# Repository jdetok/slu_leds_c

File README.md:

# SLU Fleur de Lis Lights Display
designed by Justin DeKock - Fall 2025
#
`
# [SEE USER GUIDE/INSTRUCTIONS HERE](USERGUIDE.md)
- ## [Demo Video](https://youtu.be/l19p7q0IOvI)
# [SEE BILL OF MATERIALS (ELECTRONICS PARTS) HERE](BOM.md)

## Firmware
- the device's [firmware](firmware/) is written in C++ 
- built and uploaded to Arduino with [PlatformIO](https://platformio.org/) [VSCode extension](https://platformio.org/install/ide?install=vscode)

## Printed Circuit Board (PCB)
- the [electrical schematic and the PCB](pcb/) were designed in [KiCad](https://www.kicad.org/)

## repo organization
- ### pcb/ 
    - contains KiCAD project with shematic/PCB files 
- ### firmware/
    - contains C++ firmware that gets uploaded to the arduino
    - project

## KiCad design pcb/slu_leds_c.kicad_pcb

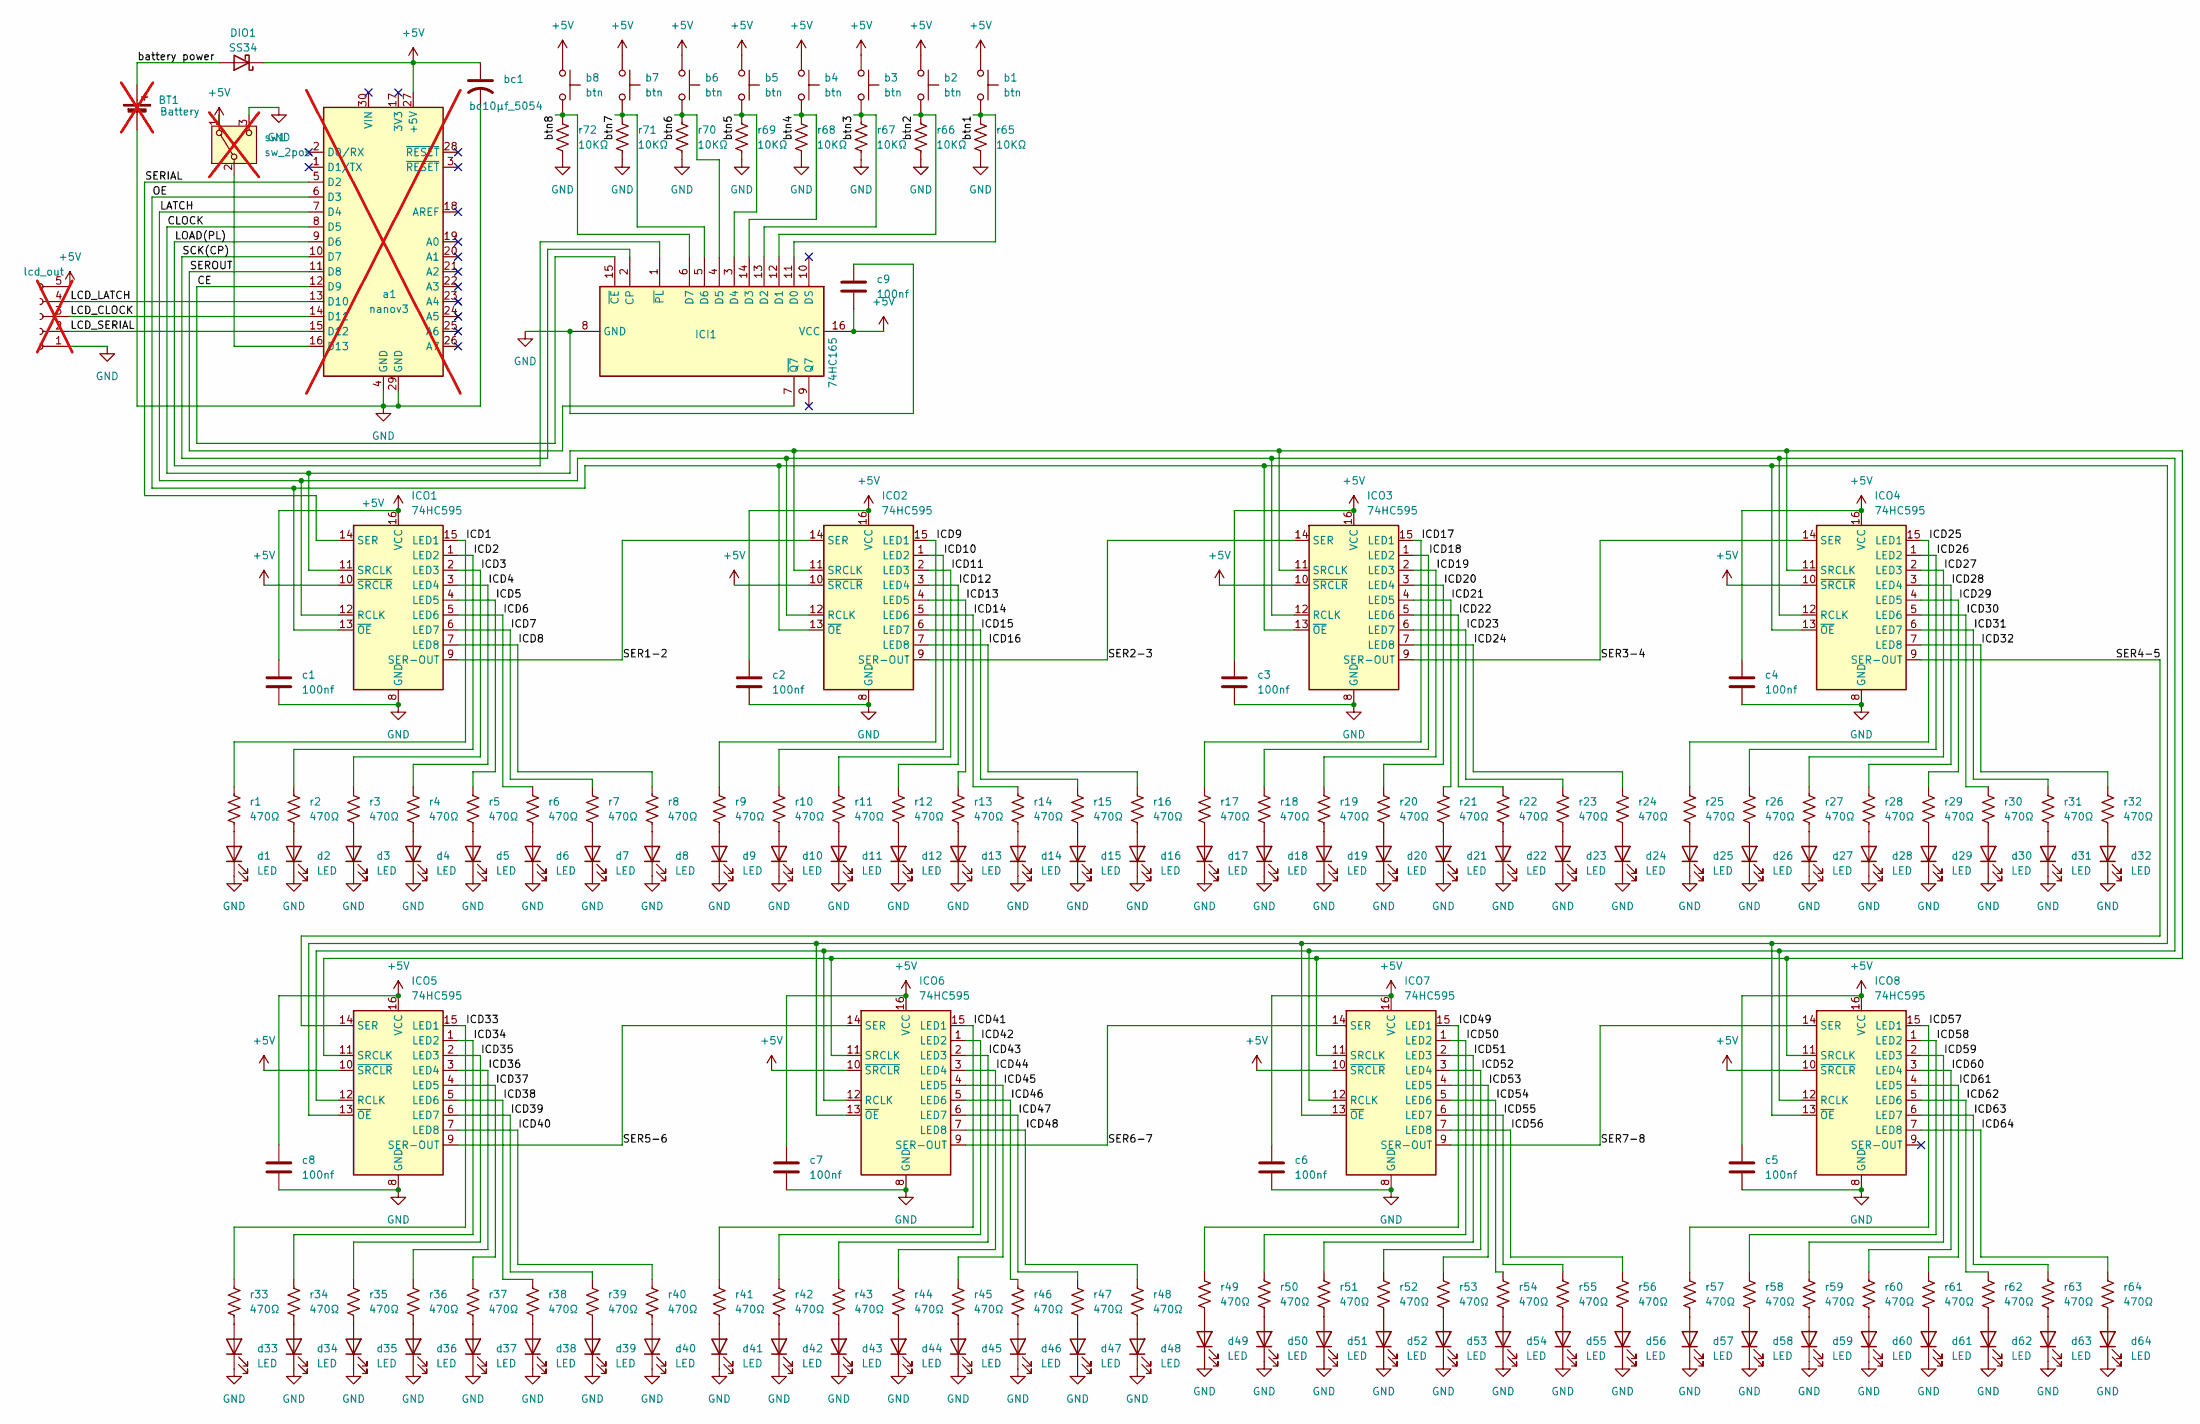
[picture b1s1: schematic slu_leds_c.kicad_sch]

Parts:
BT1: Battery; btry_18650_foirot; not fitted
DIO1: SS34; D_SMA; LCSC Part # C8678
ICI1: 74HC165; sop16_hc165; LCSC Part # C61060
ICO1, ICO2, ICO3, ICO4, ICO5, ICO6, ICO7, ICO8: 74HC595; sop16_hc595; LCSC Part # C79097
J1: lcd_out; 5pin_2.54; not fitted
a1: nanov3; not fitted
b1, b2, b3, b4, b5, b6, b7, b8: btn; btn_4x3; LCSC Part # C720477
bc1: bc10µf_5054; CP_Elec_4x5.4; LCSC Part # C3343
c1, c2, c3, c4, c5, c6, c7, c8, c9: 100nf; cap1206; LCSC Part # C24497
d1, d2, d3, d4, d5, d6, d7, d8, d9, d10, d11, d12, d13, d14, d15, d16, d17, d18, d19, d20, d21, d22, d23, d24, d25, d26, d27, d28, d29, d30, d31, d32, d33, d34, d35, d36, d37, d38, d39, d40, d41, d42, d43, d44, d45, d46, d47, d48, d49, d50, d51, d52, d53, d54, d55, d56, d57, d58, d59, d60, d61, d62, d63, d64: LED; blue_led_3528; LCSC Part # C50327302
r1, r2, r3, r4, r5, r6, r7, r8, r9, r10, r11, r12, r13, r14, r15, r16, r17, r18, r19, r20, r21, r22, r23, r24, r25, r26, r27, r28, r29, r30, r31, r32, r33, r34, r35, r36, r37, r38, r39, r40, r41, r42, r43, r44, r45, r46, r47, r48, r49, r50, r51, r52, r53, r54, r55, r56, r57, r58, r59, r60, r61, r62, r63, r64: 470Ω; r_470Ω_1206; LCSC Part # C4502
r65, r66, r67, r68, r69, r70, r71, r72: 10KΩ; r_10KΩ_1206; LCSC Part # C17902
sw1: sw_2pos; sw_2pos_spdt; not fitted

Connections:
+5V: DIO1.1 (K), ICI1.16 (VCC), ICO1.10 (~SRCLR), ICO1.16 (VCC), ICO2.10 (~SRCLR), ICO2.16 (VCC), ICO3.10 (~SRCLR), ICO3.16 (VCC), ICO4.10 (~SRCLR), ICO4.16 (VCC), ICO5.10 (~SRCLR), ICO5.16 (VCC), ICO6.10 (~SRCLR), ICO6.16 (VCC), ICO7.10 (~SRCLR), ICO7.16 (VCC), ICO8.10 (~SRCLR), ICO8.16 (VCC), J1.5, a1.27 (+5V), b1.1, b2.1, b3.1, b4.1, b5.1, b6.1, b7.1, b8.1, bc1.1, c1.1, c2.1, c3.1, c4.1, c5.1, c6.1, c7.1, c8.1, c9.2, sw1.1 (A); also elsewhere on the board
/CE: ICI1.15 (~CE), a1.12 (D9)
/CLOCK: ICO1.11 (SRCLK), ICO2.11 (SRCLK), ICO3.11 (SRCLK), ICO4.11 (SRCLK), ICO5.11 (SRCLK), ICO6.11 (SRCLK), ICO7.11 (SRCLK), ICO8.11 (SRCLK), a1.8 (D5)
/ICD1: ICO1.15 (LED1), r1.2
/ICD2: ICO1.1 (LED2), r2.2
/ICD3: ICO1.2 (LED3), r3.2
/ICD4: ICO1.3 (LED4), r4.2
/ICD5: ICO1.4 (LED5), r5.2
/ICD6: ICO1.5 (LED6), r6.2
/ICD7: ICO1.6 (LED7), r7.2
/ICD8: ICO1.7 (LED8), r8.2
/ICD9: ICO2.15 (LED1), r9.2
/ICD10: ICO2.1 (LED2), r10.2
/ICD11: ICO2.2 (LED3), r11.2
/ICD12: ICO2.3 (LED4), r12.2
/ICD13: ICO2.4 (LED5), r13.2
/ICD14: ICO2.5 (LED6), r14.2
/ICD15: ICO2.6 (LED7), r15.2
/ICD16: ICO2.7 (LED8), r16.2
/ICD17: ICO3.15 (LED1), r17.2
/ICD18: ICO3.1 (LED2), r18.2
/ICD19: ICO3.2 (LED3), r19.2
/ICD20: ICO3.3 (LED4), r20.2
/ICD21: ICO3.4 (LED5), r21.2
/ICD22: ICO3.5 (LED6), r22.2
/ICD23: ICO3.6 (LED7), r23.2
/ICD24: ICO3.7 (LED8), r24.2
/ICD25: ICO4.15 (LED1), r25.2
/ICD26: ICO4.1 (LED2), r26.2
/ICD27: ICO4.2 (LED3), r27.2
/ICD28: ICO4.3 (LED4), r28.2
/ICD29: ICO4.4 (LED5), r29.2
/ICD30: ICO4.5 (LED6), r30.2
/ICD31: ICO4.6 (LED7), r31.2
/ICD32: ICO4.7 (LED8), r32.2
/ICD33: ICO5.15 (LED1), r33.2
/ICD34: ICO5.1 (LED2), r34.2
/ICD35: ICO5.2 (LED3), r35.2
/ICD36: ICO5.3 (LED4), r36.2
/ICD37: ICO5.4 (LED5), r37.2
/ICD38: ICO5.5 (LED6), r38.2
/ICD39: ICO5.6 (LED7), r39.2
/ICD40: ICO5.7 (LED8), r40.2
/ICD41: ICO6.15 (LED1), r41.2
/ICD42: ICO6.1 (LED2), r42.2
/ICD43: ICO6.2 (LED3), r43.2
/ICD44: ICO6.3 (LED4), r44.2
/ICD45: ICO6.4 (LED5), r45.2
/ICD46: ICO6.5 (LED6), r46.2
/ICD47: ICO6.6 (LED7), r47.2
/ICD48: ICO6.7 (LED8), r48.2
/ICD49: ICO7.15 (LED1), r49.2
/ICD50: ICO7.1 (LED2), r50.2
/ICD51: ICO7.2 (LED3), r51.2
/ICD52: ICO7.3 (LED4), r52.2
/ICD53: ICO7.4 (LED5), r53.2
/ICD54: ICO7.5 (LED6), r54.2
/ICD55: ICO7.6 (LED7), r55.2
/ICD56: ICO7.7 (LED8), r56.2
/ICD57: ICO8.15 (LED1), r57.2
/ICD58: ICO8.1 (LED2), r58.2
/ICD59: ICO8.2 (LED3), r59.2
/ICD60: ICO8.3 (LED4), r60.2
/ICD61: ICO8.4 (LED5), r61.2
/ICD62: ICO8.5 (LED6), r62.2
/ICD63: ICO8.6 (LED7), r63.2
/ICD64: ICO8.7 (LED8), r64.2
/LATCH: ICO1.12 (RCLK), ICO2.12 (RCLK), ICO3.12 (RCLK), ICO4.12 (RCLK), ICO5.12 (RCLK), ICO6.12 (RCLK), ICO7.12 (RCLK), ICO8.12 (RCLK), a1.7 (D4)
/LCD_CLOCK: J1.3, a1.14 (D11)
/LCD_LATCH: J1.4, a1.13 (D10)
/LCD_SERIAL: J1.2, a1.15 (D12)
/LOAD(PL): ICI1.1 (~PL), a1.9 (D6)
/OE: ICO1.13 (~OE), ICO2.13 (~OE), ICO3.13 (~OE), ICO4.13 (~OE), ICO5.13 (~OE), ICO6.13 (~OE), ICO7.13 (~OE), ICO8.13 (~OE), a1.6 (D3)
/SCK(CP): ICI1.2 (CP), a1.10 (D7)
/SER1-2: ICO1.9 (SER-OUT), ICO2.14 (SER)
/SER2-3: ICO2.9 (SER-OUT), ICO3.14 (SER)
/SER3-4: ICO3.9 (SER-OUT), ICO4.14 (SER)
/SER4-5: ICO4.9 (SER-OUT), ICO5.14 (SER)
/SER5-6: ICO5.9 (SER-OUT), ICO6.14 (SER)
/SER6-7: ICO6.9 (SER-OUT), ICO7.14 (SER)
/SER7-8: ICO7.9 (SER-OUT), ICO8.14 (SER)
/SERIAL: ICO1.14 (SER), a1.5 (D2)
/SEROUT: ICI1.7 (~Q7), a1.11 (D8)
/btn1: ICI1.11 (D0), b1.2, r65.1
/btn2: ICI1.12 (D1), b2.2, r66.1
/btn3: ICI1.13 (D2), b3.2, r67.1
/btn4: ICI1.14 (D3), b4.2, r68.1
/btn5: ICI1.3 (D4), b5.2, r69.1
/btn6: ICI1.4 (D5), b6.2, r70.1
/btn7: ICI1.5 (D6), b7.2, r71.1
/btn8: ICI1.6 (D7), b8.2, r72.1
GND: BT1.2 (-), ICI1.8 (GND), ICO1.8 (GND), ICO2.8 (GND), ICO3.8 (GND), ICO4.8 (GND), ICO5.8 (GND), ICO6.8 (GND), ICO7.8 (GND), ICO8.8 (GND), J1.1, a1.4 (GND), a1.29 (GND), bc1.2, c1.2, c2.2, c3.2, c4.2, c5.2, c6.2, c7.2, c8.2, c9.1, d1.1 (K), d2.1 (K), d3.1 (K), d4.1 (K), d5.1 (K), d6.1 (K), d7.1 (K), d8.1 (K), d9.1 (K), d10.1 (K), d11.1 (K), d12.1 (K), d13.1 (K), d14.1 (K), d15.1 (K), d16.1 (K), d17.1 (K), d18.1 (K), d19.1 (K), d20.1 (K), d21.1 (K), d22.1 (K), d23.1 (K), d24.1 (K), d25.1 (K), d26.1 (K), d27.1 (K), d28.1 (K), d29.1 (K), d30.1 (K), d31.1 (K), d32.1 (K), d33.1 (K), d34.1 (K), d35.1 (K), d36.1 (K), d37.1 (K), d38.1 (K), d39.1 (K), d40.1 (K), d41.1 (K), d42.1 (K), d43.1 (K), d44.1 (K), d45.1 (K), d46.1 (K), d47.1 (K), d48.1 (K), d49.1 (K), d50.1 (K), d51.1 (K), d52.1 (K), d53.1 (K), d54.1 (K), d55.1 (K), d56.1 (K), d57.1 (K), d58.1 (K), d59.1 (K), d60.1 (K), d61.1 (K), d62.1 (K), d63.1 (K), d64.1 (K), r65.2, r66.2, r67.2, r68.2, r69.2, r70.2, r71.2, r72.2, sw1.3 (C); also elsewhere on the board
unnamed: BT1.1 (+), DIO1.2 (A)
unnamed: a1.16 (D13), sw1.2 (B)
unnamed: d1.2 (A), r1.1
unnamed: d2.2 (A), r2.1
unnamed: d3.2 (A), r3.1
unnamed: d4.2 (A), r4.1
unnamed: d5.2 (A), r5.1
unnamed: d6.2 (A), r6.1
unnamed: d7.2 (A), r7.1
unnamed: d8.2 (A), r8.1
unnamed: d9.2 (A), r9.1
unnamed: d10.2 (A), r10.1
unnamed: d11.2 (A), r11.1
unnamed: d12.2 (A), r12.1
unnamed: d13.2 (A), r13.1
unnamed: d14.2 (A), r14.1
unnamed: d15.2 (A), r15.1
unnamed: d16.2 (A), r16.1
unnamed: d17.2 (A), r17.1
unnamed: d18.2 (A), r18.1
unnamed: d19.2 (A), r19.1
unnamed: d20.2 (A), r20.1
unnamed: d21.2 (A), r21.1
unnamed: d22.2 (A), r22.1
unnamed: d23.2 (A), r23.1
unnamed: d24.2 (A), r24.1
unnamed: d25.2 (A), r25.1
unnamed: d26.2 (A), r26.1
unnamed: d27.2 (A), r27.1
unnamed: d28.2 (A), r28.1
unnamed: d29.2 (A), r29.1
unnamed: d30.2 (A), r30.1
unnamed: d31.2 (A), r31.1
unnamed: d32.2 (A), r32.1
unnamed: d33.2 (A), r33.1
unnamed: d34.2 (A), r34.1
unnamed: d35.2 (A), r35.1
unnamed: d36.2 (A), r36.1
unnamed: d37.2 (A), r37.1
unnamed: d38.2 (A), r38.1
unnamed: d39.2 (A), r39.1
unnamed: d40.2 (A), r40.1
unnamed: d41.2 (A), r41.1
unnamed: d42.2 (A), r42.1
unnamed: d43.2 (A), r43.1
unnamed: d44.2 (A), r44.1
unnamed: d45.2 (A), r45.1
unnamed: d46.2 (A), r46.1
unnamed: d47.2 (A), r47.1
unnamed: d48.2 (A), r48.1
unnamed: d49.2 (A), r49.1
unnamed: d50.2 (A), r50.1
unnamed: d51.2 (A), r51.1
unnamed: d52.2 (A), r52.1
unnamed: d53.2 (A), r53.1
unnamed: d54.2 (A), r54.1
unnamed: d55.2 (A), r55.1
unnamed: d56.2 (A), r56.1
unnamed: d57.2 (A), r57.1
unnamed: d58.2 (A), r58.1
unnamed: d59.2 (A), r59.1
unnamed: d60.2 (A), r60.1
unnamed: d61.2 (A), r61.1
unnamed: d62.2 (A), r62.1
unnamed: d63.2 (A), r63.1
unnamed: d64.2 (A), r64.1

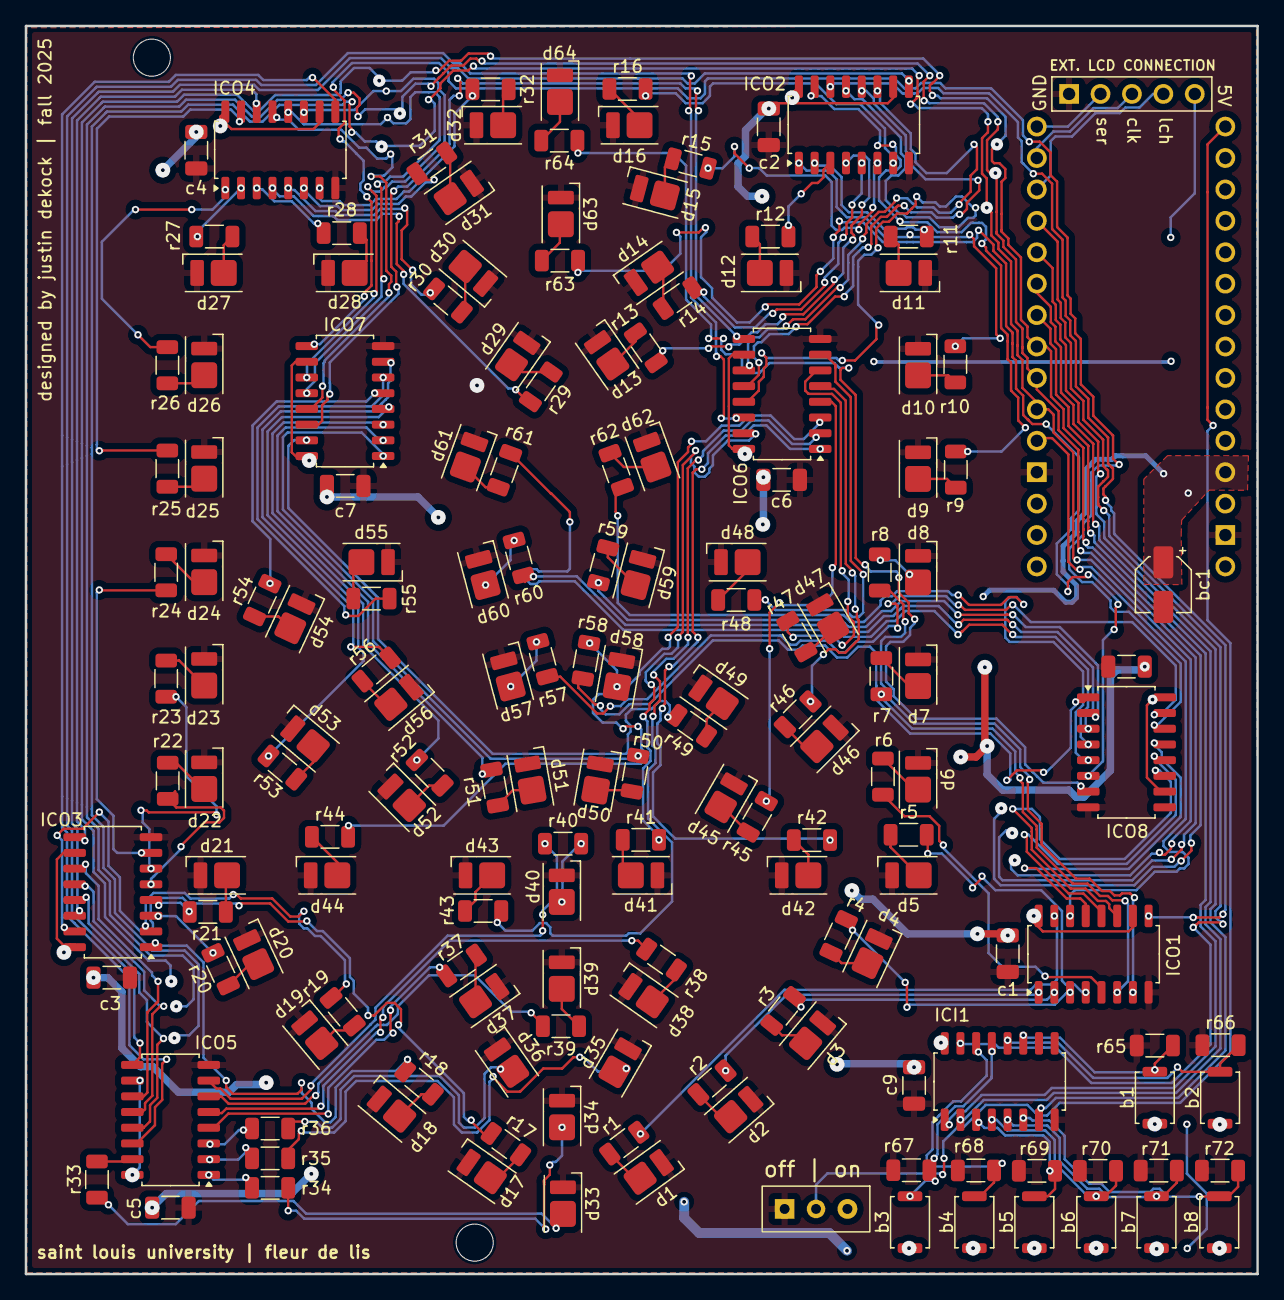
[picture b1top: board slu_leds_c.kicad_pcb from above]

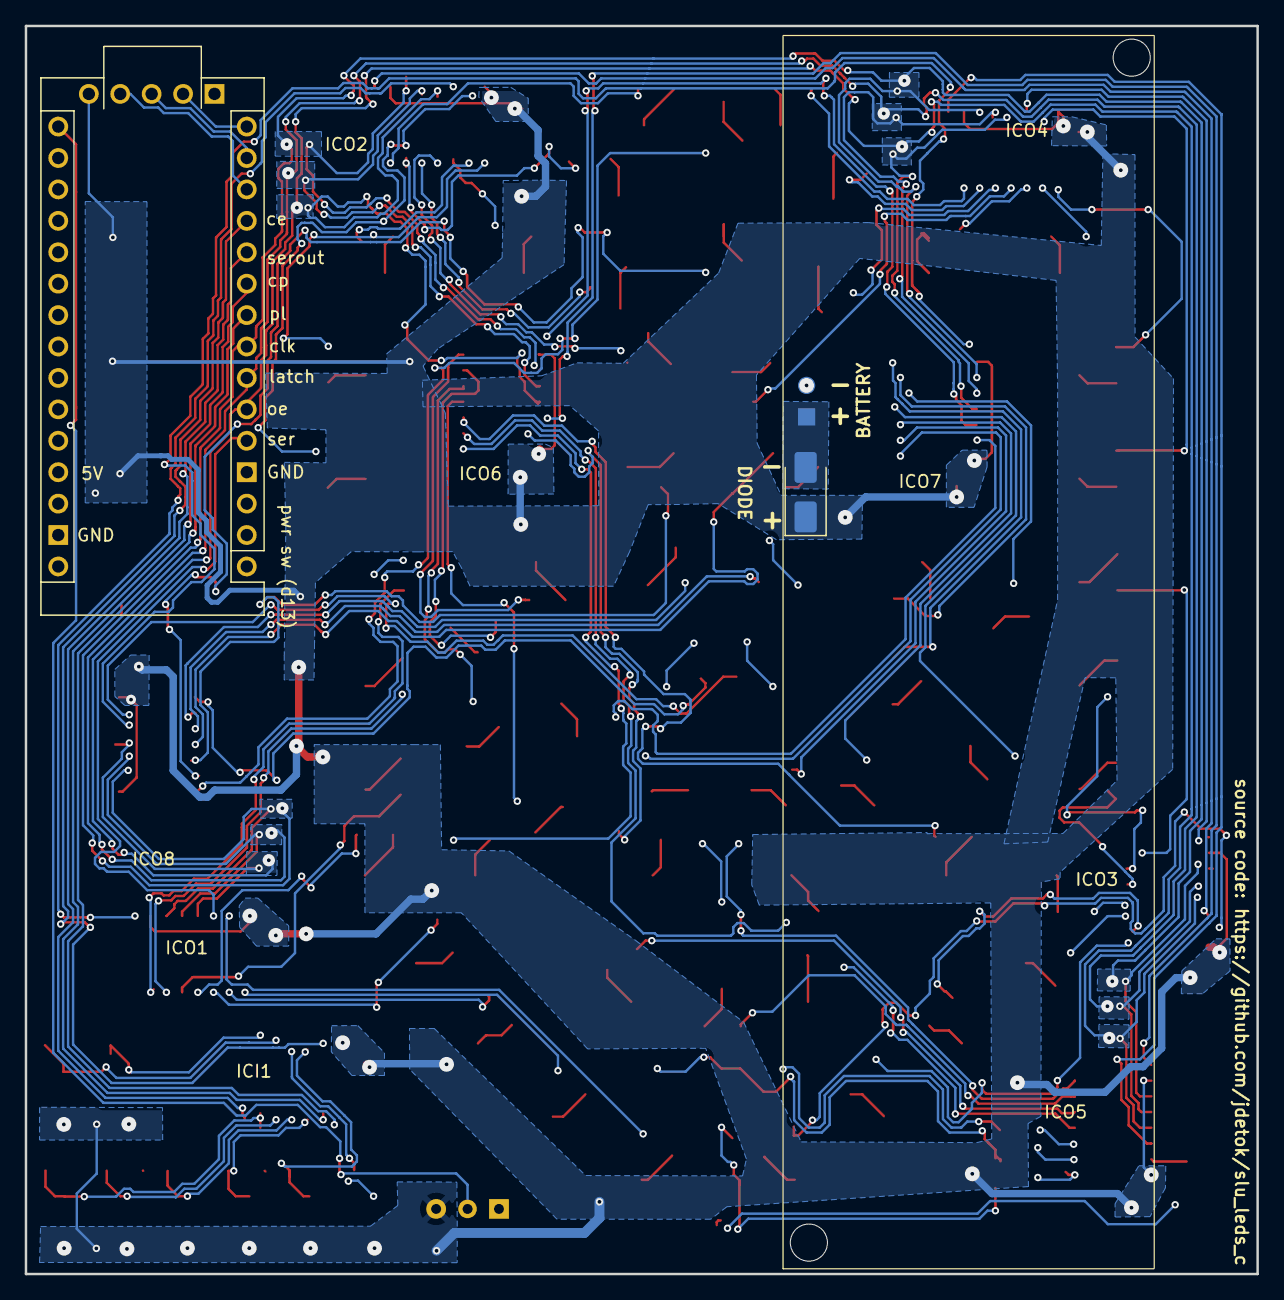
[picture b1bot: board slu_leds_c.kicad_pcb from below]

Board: 2 copper layers, 99.6 x 100.9 mm, 168 parts (3 on the bottom side), 158 nets.

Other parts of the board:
BATTERY: Battery; btry_18650_foirot
DIODE: SS34; D_SMA

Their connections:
+5V: DIODE.1 (K); also elsewhere on the board
/battery power: BATTERY.1 (+), DIODE.2 (A)
GND: BATTERY.2 (-); also elsewhere on the board

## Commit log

2025-11-26 init
2025-11-26 repurposing remote branch
2025-11-26 arduino pin pre processors
2025-11-26 initial working c++ layout
2025-11-27 basic functionality to read buttons from 74HC165
2025-11-27 big refactor, structs for LED brightness and button state
2025-11-27 brightness adjustment, struct refactors
2025-11-28 lights buttons refactor
2025-11-28 refactor to all embedded structs
2025-11-28 basic control struct functionality working
2025-11-28 WORKING RECOVERY
2025-11-28 basic recovery for lcd
2025-11-30 basic bit chaser is working
2025-12-01 recovery using persistent bit map
2025-12-01 track chase index location
2025-12-01 speed buttons
2025-12-01 chase4 option - each button has a purpose now
2025-12-01 changed fill and empty to direct memset
2025-12-01 major refactor, good working recovery on breadboard
2025-12-01 more cleanup, particularly serial prints
2025-12-01 pre defined speed modes
2025-12-01 maximum brightness edit while pulsing
2025-12-01 smoother brightness adjust
2025-12-08 Working version with assembled PCB
2025-12-09 "manipulate wired order of lights"
2025-12-09 calculate virtual positions once, store in array
2025-12-10 working refactor, fix bug of light flash when turns on
2025-12-10 move run func to main.cpp
2025-12-11 user instruction, demo vid, src finalization
2025-12-11 remove unecessary default pio dirs
